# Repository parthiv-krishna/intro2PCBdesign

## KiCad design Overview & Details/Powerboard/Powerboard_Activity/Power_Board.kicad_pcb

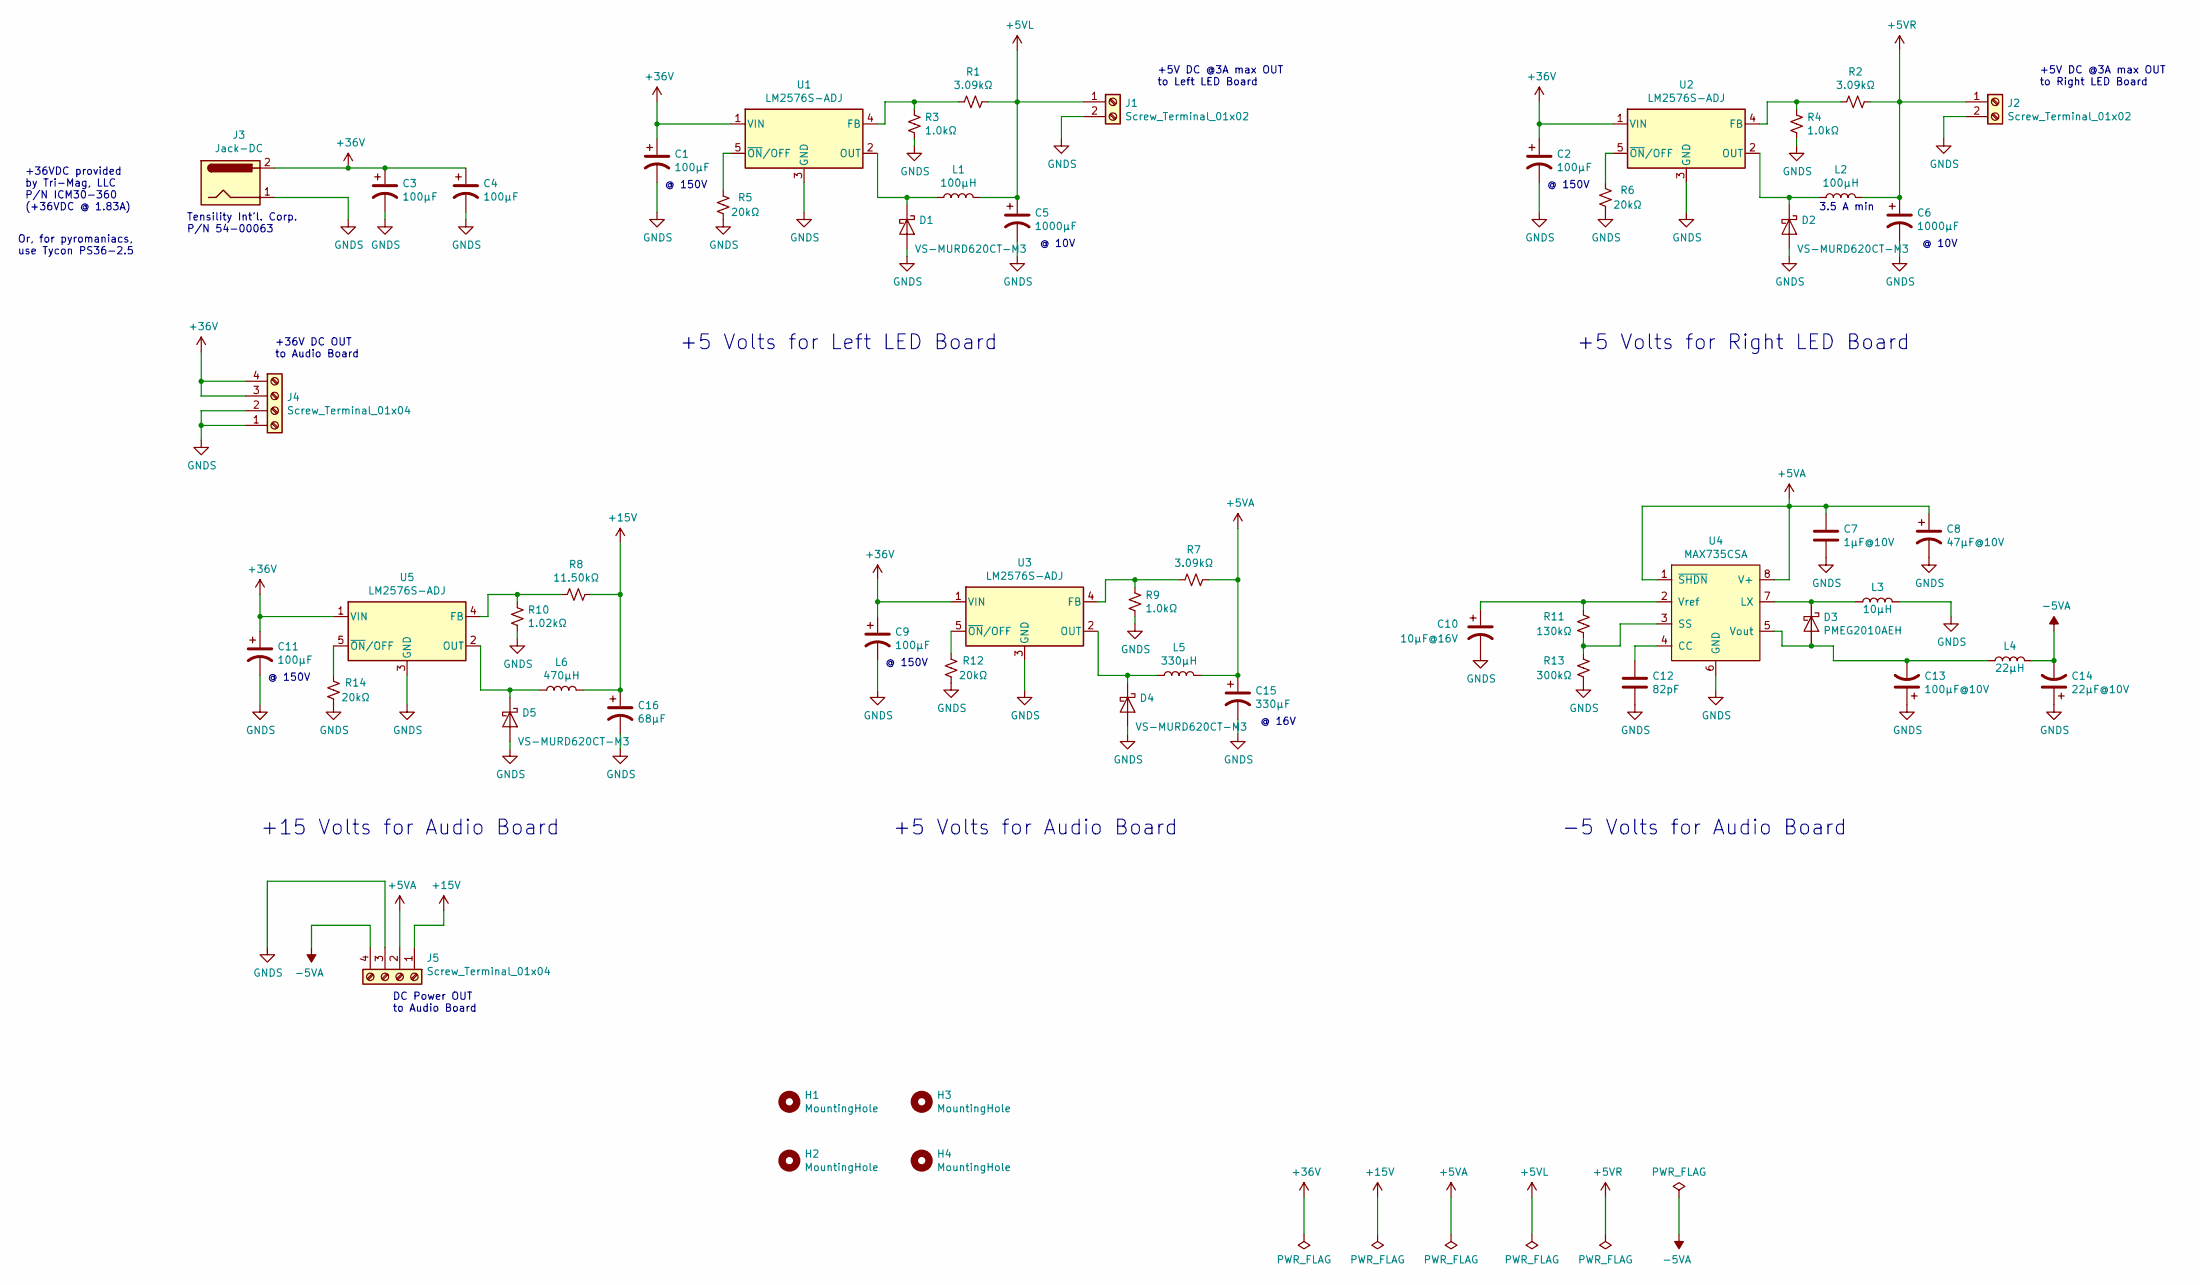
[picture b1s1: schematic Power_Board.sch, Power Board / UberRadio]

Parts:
C1, C2, C9, C11: 100µF; PCR1J101MCL1GS
C3, C4: 100μF; PCR1J101MCL1GS
C5, C6: 1000µF; CP_EIA-7361-438_AVX-U_Pad2.18x3.30mm_HandSolder
C7: 1μF@10V; C_0805_2012Metric_Pad1.15x1.40mm_HandSolder
C8: 47μF@10V; CP_Elec_6.3x5.7
C10: 10μF@16V; C_0805_2012Metric_Pad1.15x1.40mm_HandSolder
C12: 82pF; C_0805_2012Metric_Pad1.15x1.40mm_HandSolder
C13: 100μF@10V; C_1210_3225Metric_Pad1.42x2.65mm_HandSolder
C14: 22μF@10V; C_0805_2012Metric_Pad1.15x1.40mm_HandSolder
C15: 330µF; CP_Elec_8x10
C16: 68µF; CP_Elec_10x10
D1, D2, D4, D5: VS-MURD620CT-M3; TO-252AA_TabPin4
D3: PMEG2010AEH; D_SOD-123F
H1, H2, H3, H4: MountingHole; MountingHole_5.3mm_M5
J1, J2: Screw_Terminal_01x02; AVX-Wire-To-Board-1x2
J3: Jack-DC; BarrelJack_Power_2.1x5.5mm_11mmThruHole_PanelMount
J4, J5: Screw_Terminal_01x04; AVX-Wire-To-Board-1x4
L1, L2: 100µH; Eaton_CTX100-2-52-R
L3: 10μH; L_Taiyo-Yuden_NR-10050_9.8x10.0mm_HandSoldering
L4: 22μH; L_Taiyo-Yuden_NR-60xx_HandSoldering
L5: 330µH; L_Toroid_Horizontal_D21.8mm_P19.60mm_Bourns_2100
L6: 470µH; L_Toroid_Horizontal_D21.8mm_P19.60mm_Bourns_2100
R1, R2, R7: 3.09kΩ; R_0805_2012Metric_Pad1.15x1.40mm_HandSolder
R3, R4, R9: 1.0kΩ; R_0805_2012Metric_Pad1.15x1.40mm_HandSolder
R5, R6, R12, R14: 20kΩ; R_0805_2012Metric_Pad1.15x1.40mm_HandSolder
R8: 11.50kΩ; R_0805_2012Metric_Pad1.15x1.40mm_HandSolder
R10: 1.02kΩ; R_0805_2012Metric_Pad1.15x1.40mm_HandSolder
R11: 130kΩ; R_0805_2012Metric_Pad1.15x1.40mm_HandSolder
R13: 300kΩ; R_0805_2012Metric_Pad1.15x1.40mm_HandSolder
U1, U2, U3, U5: LM2576S-ADJ; TO-263-5_TabPin3
U4: MAX735CSA; SOP-8_3.9x4.9mm_P1.27mm

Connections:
+5VA: C7.1, C8.1, C15.1, J5.2, L5.2, R7.1, U4.1 (~SHDN), U4.8 (V+)
+5VL: C5.1, J1.1, L1.2, R1.1
+5VR: C6.1, J2.1, L2.2, R2.1
+15V: C16.1, J5.1, L6.2, R8.1
+36V: C1.1, C2.1, C3.1, C4.1, C9.1, C11.1, J3.2, J4.3 (Pin_2), J4.4 (Pin_1), U1.1 (VIN), U2.1 (VIN), U3.1 (VIN), U5.1 (VIN)
-5VA: C14.2, J5.4, L4.2
GNDS: C1.2, C2.2, C3.2, C4.2, C5.2, C6.2, C7.2, C8.2, C9.2, C10.2, C11.2, C12.2, C13.1, C14.1, C15.2, C16.2, D1.2 (A), D2.2 (A), D4.2 (A), D5.2 (A), J1.2, J2.2, J3.1, J4.1 (Pin_4), J4.2 (ePin_3), J5.3, L3.2, R3.1, R4.1, R5.1, R6.1, R9.1, R10.1, R12.1, R13.2, R14.1, U1.3 (GND), U2.3 (GND), U3.3 (GND), U4.6 (GND), U5.3 (GND)
unnamed: C10.1, R11.1, U4.2 (Vref)
unnamed: C12.1, U4.4 (CC)
unnamed: C13.2, D3.2 (A), L4.1, U4.5 (Vout)
unnamed: D1.1 (K), L1.1, U1.2 (OUT)
unnamed: D2.1 (K), L2.1, U2.2 (OUT)
unnamed: D3.1 (K), L3.1, U4.7 (LX)
unnamed: D4.1 (K), L5.1, U3.2 (OUT)
unnamed: D5.1 (K), L6.1, U5.2 (OUT)
unnamed: R1.2, R3.2, U1.4 (FB)
unnamed: R2.2, R4.2, U2.4 (FB)
unnamed: R5.2, U1.5 (~ON~/OFF)
unnamed: R6.2, U2.5 (~ON~/OFF)
unnamed: R7.2, R9.2, U3.4 (FB)
unnamed: R8.2, R10.2, U5.4 (FB)
unnamed: R11.2, R13.1, U4.3 (SS)
unnamed: R12.2, U3.5 (~ON~/OFF)
unnamed: R14.2, U5.5 (~ON~/OFF)

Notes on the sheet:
Tensility Int’l. Corp. P/N 54-00063
+36VDC provided by Tri-Mag, LLC P/N ICM30-360 (+36VDC @ 1.83A)
Or, for pyromaniacs, use Tycon PS36-2.5
+5 Volts for Left LED Board
+5 Volts for Right LED Board
+15 Volts for Audio Board
+5 Volts for Audio Board
-5 Volts for Audio Board
@ 150V
3.5 A min
@ 10V
@ 16V
+36V DC OUT to Audio Board
DC Power OUT to Audio Board
+5V DC @3A max OUT to Left LED Board
+5V DC @3A max OUT to Right LED Board

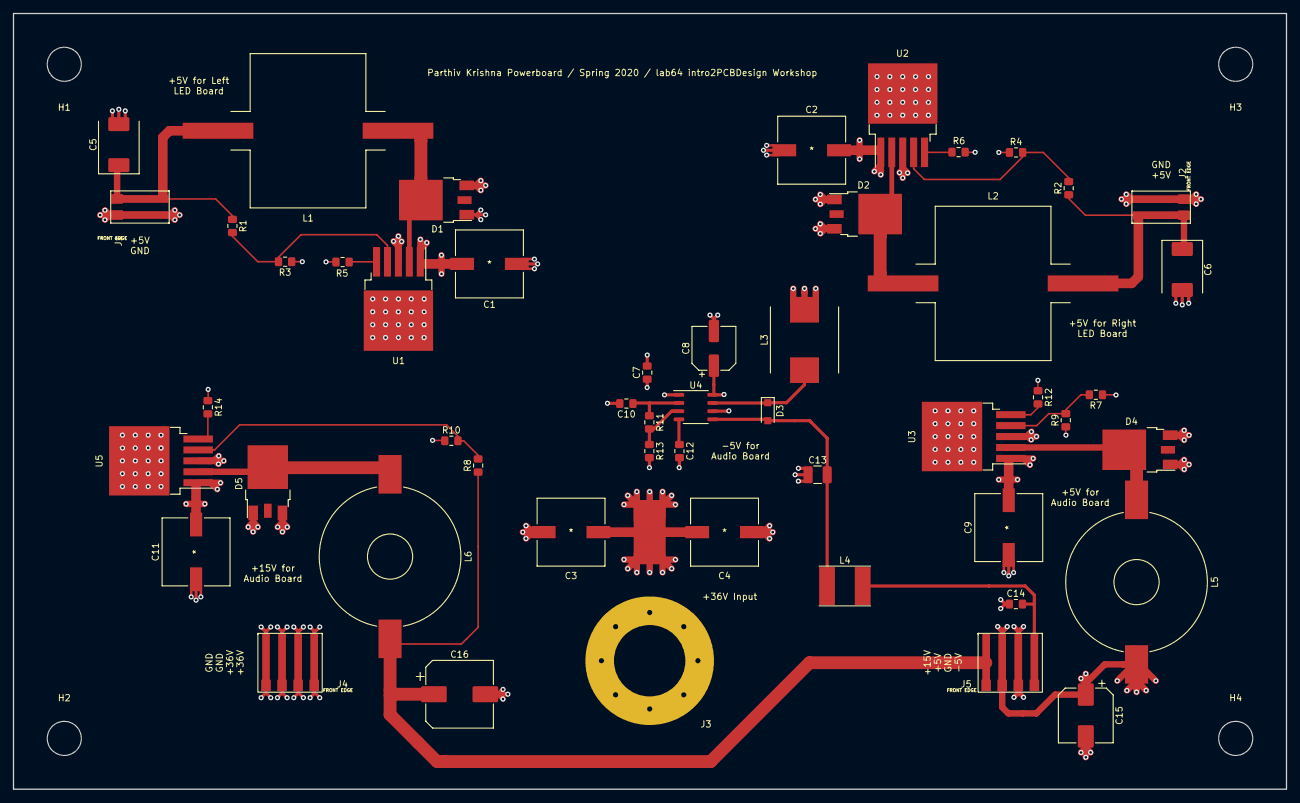
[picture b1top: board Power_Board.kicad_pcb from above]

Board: 4 copper layers, 198.0 x 120.7 mm, 55 parts (0 on the bottom side), 24 nets.

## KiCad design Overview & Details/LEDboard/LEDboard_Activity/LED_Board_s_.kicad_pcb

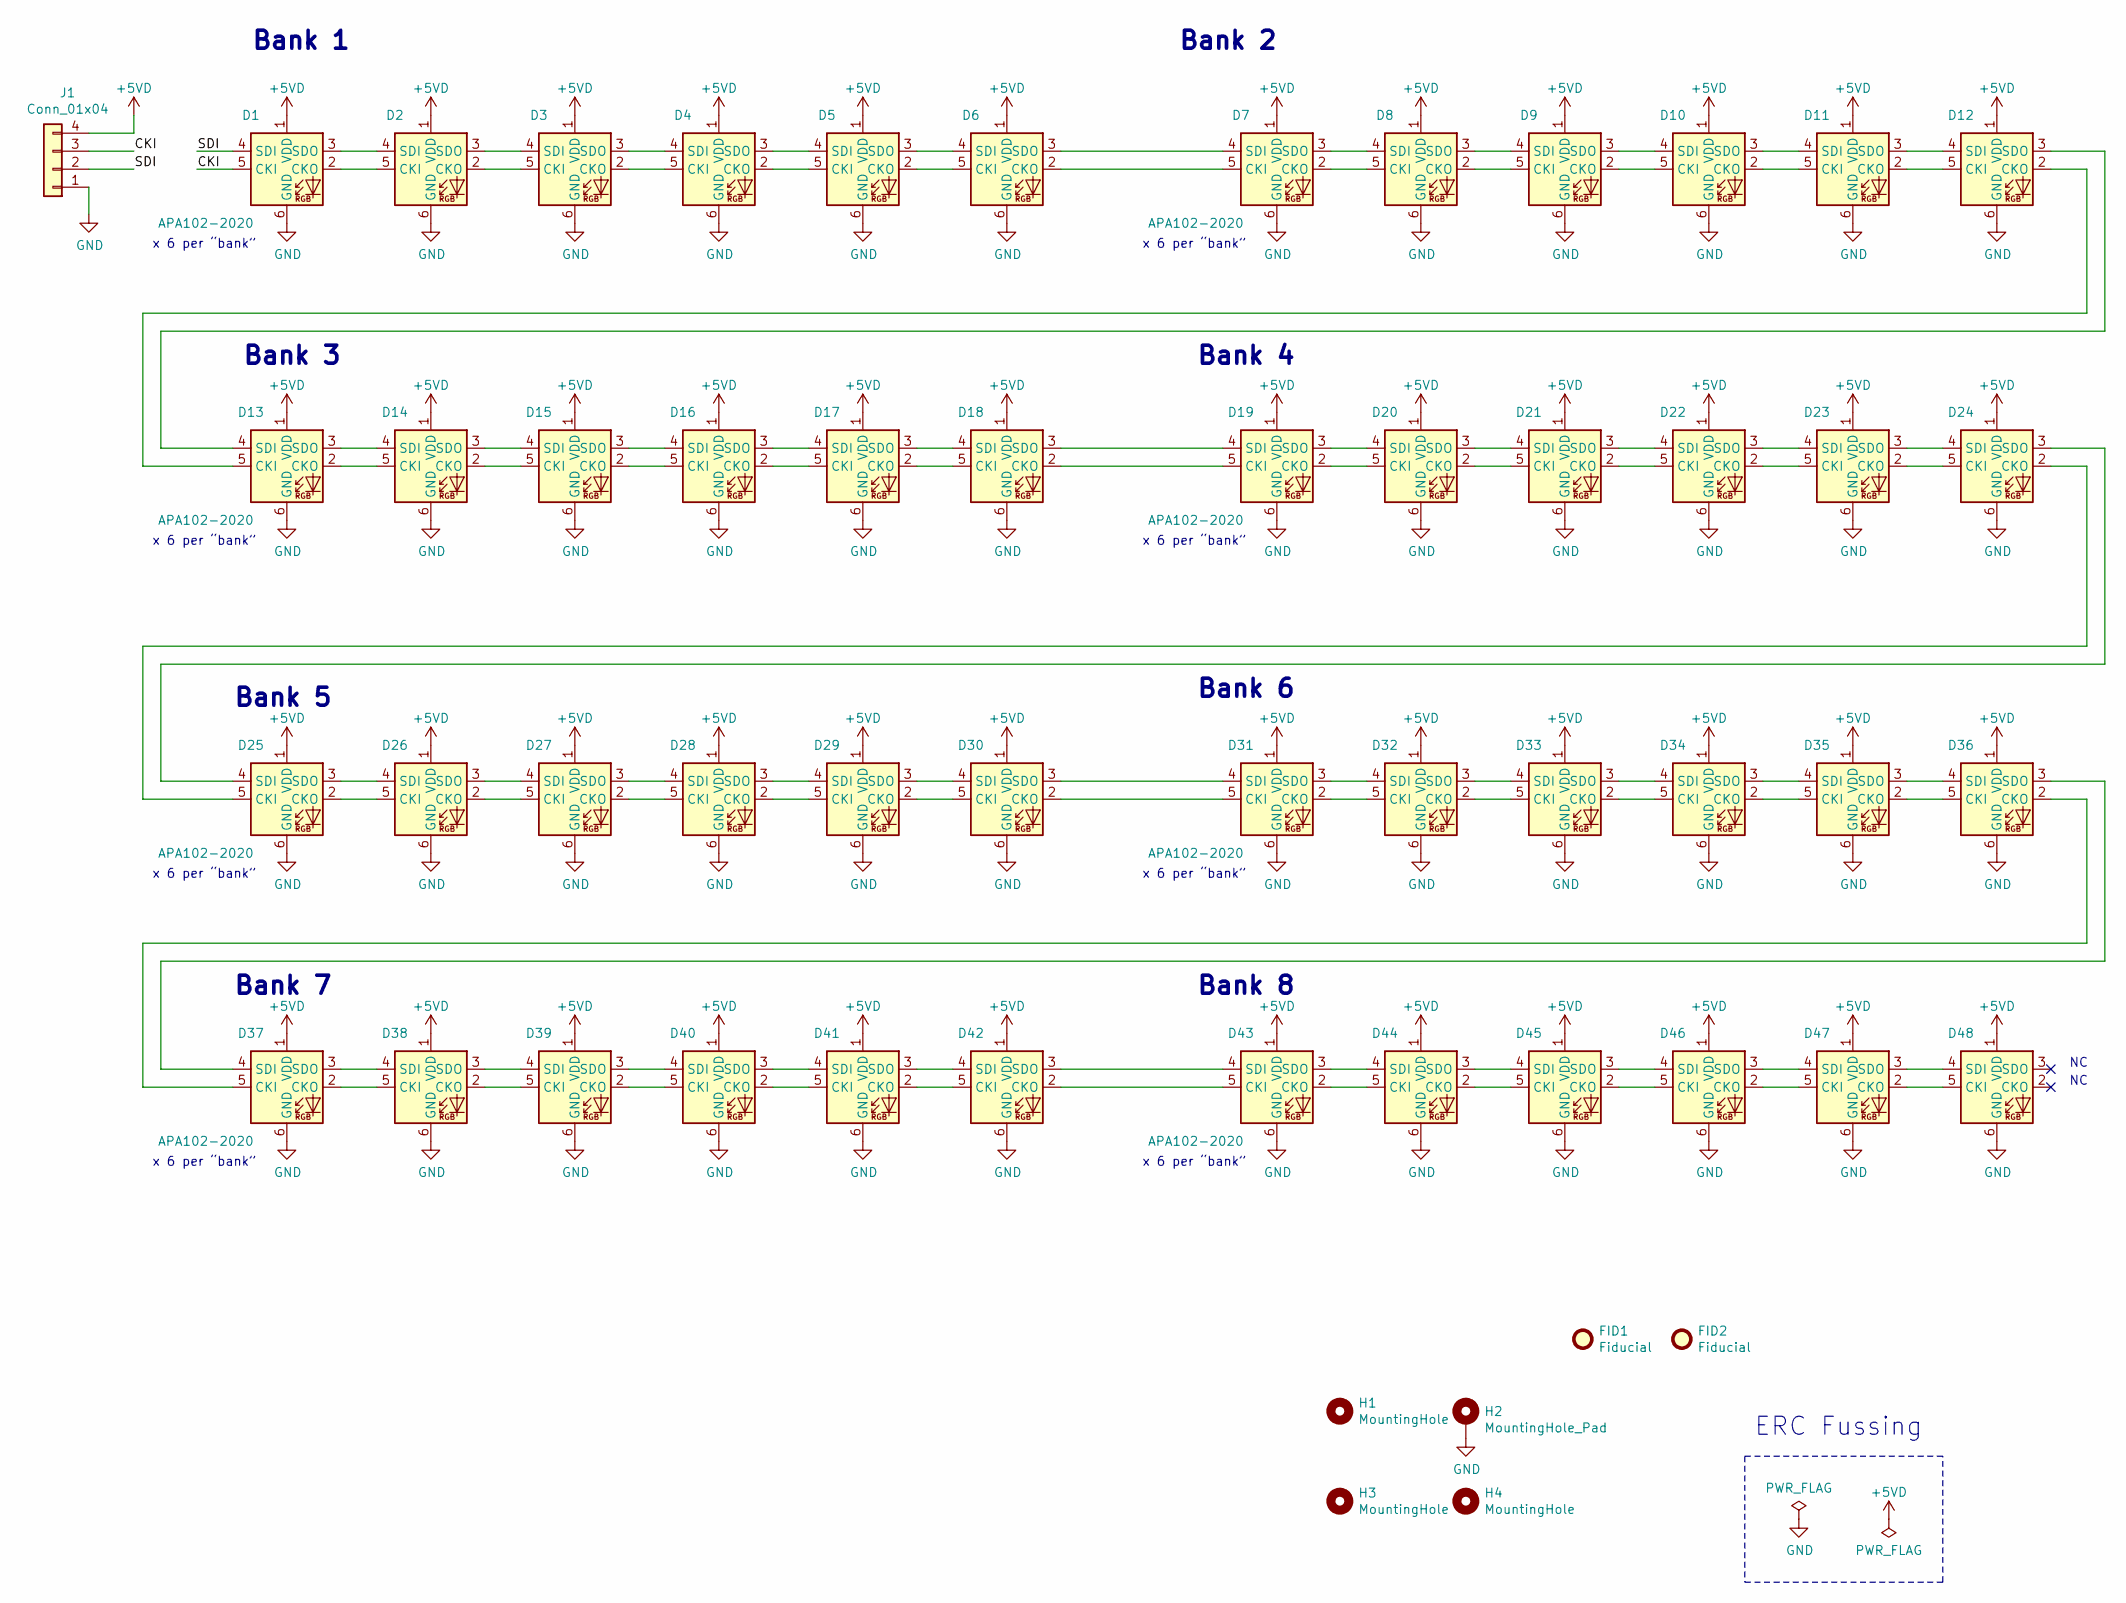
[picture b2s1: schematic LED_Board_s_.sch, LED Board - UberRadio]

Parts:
D1, D2, D3, D4, D5, D6, D7, D8, D9, D10, D11, D12, D13, D14, D15, D16, D17, D18, D19, D20, D21, D22, D23, D24, D25, D26, D27, D28, D29, D30, D31, D32, D33, D34, D35, D36, D37, D38, D39, D40, D41, D42, D43, D44, D45, D46, D47, D48: APA102-2020; LED-APA102-2020
FID1, FID2: Fiducial; Fiducial_0.5mm_Mask1mm
H1, H3, H4: MountingHole; MountingHole_3.5mm_Pad
H2: MountingHole_Pad; MountingHole_3.5mm_Pad_Via
J1: Conn_01x04; PinHeader_1x04_P2.54mm_Vertical

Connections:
+5VD: D1.1 (VDD), D2.1 (VDD), D3.1 (VDD), D4.1 (VDD), D5.1 (VDD), D6.1 (VDD), D7.1 (VDD), D8.1 (VDD), D9.1 (VDD), D10.1 (VDD), D11.1 (VDD), D12.1 (VDD), D13.1 (VDD), D14.1 (VDD), D15.1 (VDD), D16.1 (VDD), D17.1 (VDD), D18.1 (VDD), D19.1 (VDD), D20.1 (VDD), D21.1 (VDD), D22.1 (VDD), D23.1 (VDD), D24.1 (VDD), D25.1 (VDD), D26.1 (VDD), D27.1 (VDD), D28.1 (VDD), D29.1 (VDD), D30.1 (VDD), D31.1 (VDD), D32.1 (VDD), D33.1 (VDD), D34.1 (VDD), D35.1 (VDD), D36.1 (VDD), D37.1 (VDD), D38.1 (VDD), D39.1 (VDD), D40.1 (VDD), D41.1 (VDD), D42.1 (VDD), D43.1 (VDD), D44.1 (VDD), D45.1 (VDD), D46.1 (VDD), D47.1 (VDD), D48.1 (VDD), J1.4
/CKI: D1.5 (CKI), J1.3
/SDI: D1.4 (SDI), J1.2
GND: D1.6 (GND), D2.6 (GND), D3.6 (GND), D4.6 (GND), D5.6 (GND), D6.6 (GND), D7.6 (GND), D8.6 (GND), D9.6 (GND), D10.6 (GND), D11.6 (GND), D12.6 (GND), D13.6 (GND), D14.6 (GND), D15.6 (GND), D16.6 (GND), D17.6 (GND), D18.6 (GND), D19.6 (GND), D20.6 (GND), D21.6 (GND), D22.6 (GND), D23.6 (GND), D24.6 (GND), D25.6 (GND), D26.6 (GND), D27.6 (GND), D28.6 (GND), D29.6 (GND), D30.6 (GND), D31.6 (GND), D32.6 (GND), D33.6 (GND), D34.6 (GND), D35.6 (GND), D36.6 (GND), D37.6 (GND), D38.6 (GND), D39.6 (GND), D40.6 (GND), D41.6 (GND), D42.6 (GND), D43.6 (GND), D44.6 (GND), D45.6 (GND), D46.6 (GND), D47.6 (GND), D48.6 (GND), H2.1, J1.1
unnamed: D1.2 (CKO), D2.5 (CKI)
unnamed: D1.3 (SDO), D2.4 (SDI)
unnamed: D2.2 (CKO), D3.5 (CKI)
unnamed: D2.3 (SDO), D3.4 (SDI)
unnamed: D3.2 (CKO), D4.5 (CKI)
unnamed: D3.3 (SDO), D4.4 (SDI)
unnamed: D4.2 (CKO), D5.5 (CKI)
unnamed: D4.3 (SDO), D5.4 (SDI)
unnamed: D5.2 (CKO), D6.5 (CKI)
unnamed: D5.3 (SDO), D6.4 (SDI)
unnamed: D6.2 (CKO), D7.5 (CKI)
unnamed: D6.3 (SDO), D7.4 (SDI)
unnamed: D7.2 (CKO), D8.5 (CKI)
unnamed: D7.3 (SDO), D8.4 (SDI)
unnamed: D8.2 (CKO), D9.5 (CKI)
unnamed: D8.3 (SDO), D9.4 (SDI)
unnamed: D10.2 (CKO), D11.5 (CKI)
unnamed: D10.3 (SDO), D11.4 (SDI)
unnamed: D9.3 (SDO), D10.4 (SDI)
unnamed: D9.2 (CKO), D10.5 (CKI)
unnamed: D11.2 (CKO), D12.5 (CKI)
unnamed: D11.3 (SDO), D12.4 (SDI)
unnamed: D12.2 (CKO), D13.5 (CKI)
unnamed: D12.3 (SDO), D13.4 (SDI)
unnamed: D13.2 (CKO), D14.5 (CKI)
unnamed: D13.3 (SDO), D14.4 (SDI)
unnamed: D14.2 (CKO), D15.5 (CKI)
unnamed: D14.3 (SDO), D15.4 (SDI)
unnamed: D15.2 (CKO), D16.5 (CKI)
unnamed: D15.3 (SDO), D16.4 (SDI)
unnamed: D16.2 (CKO), D17.5 (CKI)
unnamed: D16.3 (SDO), D17.4 (SDI)
unnamed: D17.2 (CKO), D18.5 (CKI)
unnamed: D17.3 (SDO), D18.4 (SDI)
unnamed: D18.2 (CKO), D19.5 (CKI)
unnamed: D18.3 (SDO), D19.4 (SDI)
unnamed: D19.2 (CKO), D20.5 (CKI)
unnamed: D19.3 (SDO), D20.4 (SDI)
unnamed: D20.2 (CKO), D21.5 (CKI)
unnamed: D20.3 (SDO), D21.4 (SDI)
unnamed: D21.2 (CKO), D22.5 (CKI)
unnamed: D21.3 (SDO), D22.4 (SDI)
unnamed: D22.2 (CKO), D23.5 (CKI)
unnamed: D22.3 (SDO), D23.4 (SDI)
unnamed: D23.2 (CKO), D24.5 (CKI)
unnamed: D23.3 (SDO), D24.4 (SDI)
unnamed: D24.2 (CKO), D25.5 (CKI)
unnamed: D24.3 (SDO), D25.4 (SDI)
unnamed: D25.2 (CKO), D26.5 (CKI)
unnamed: D25.3 (SDO), D26.4 (SDI)
unnamed: D26.2 (CKO), D27.5 (CKI)
unnamed: D26.3 (SDO), D27.4 (SDI)
unnamed: D27.2 (CKO), D28.5 (CKI)
unnamed: D27.3 (SDO), D28.4 (SDI)
unnamed: D28.2 (CKO), D29.5 (CKI)
unnamed: D28.3 (SDO), D29.4 (SDI)
unnamed: D29.2 (CKO), D30.5 (CKI)
unnamed: D29.3 (SDO), D30.4 (SDI)
unnamed: D30.2 (CKO), D31.5 (CKI)
unnamed: D30.3 (SDO), D31.4 (SDI)
unnamed: D31.2 (CKO), D32.5 (CKI)
unnamed: D31.3 (SDO), D32.4 (SDI)
unnamed: D32.2 (CKO), D33.5 (CKI)
unnamed: D32.3 (SDO), D33.4 (SDI)
unnamed: D33.2 (CKO), D34.5 (CKI)
unnamed: D33.3 (SDO), D34.4 (SDI)
unnamed: D34.2 (CKO), D35.5 (CKI)
unnamed: D34.3 (SDO), D35.4 (SDI)
unnamed: D35.2 (CKO), D36.5 (CKI)
unnamed: D35.3 (SDO), D36.4 (SDI)
unnamed: D36.2 (CKO), D37.5 (CKI)
unnamed: D36.3 (SDO), D37.4 (SDI)
unnamed: D37.2 (CKO), D38.5 (CKI)
unnamed: D37.3 (SDO), D38.4 (SDI)
unnamed: D38.2 (CKO), D39.5 (CKI)
unnamed: D38.3 (SDO), D39.4 (SDI)
unnamed: D39.2 (CKO), D40.5 (CKI)
unnamed: D39.3 (SDO), D40.4 (SDI)
unnamed: D40.2 (CKO), D41.5 (CKI)
unnamed: D40.3 (SDO), D41.4 (SDI)
unnamed: D41.2 (CKO), D42.5 (CKI)
unnamed: D41.3 (SDO), D42.4 (SDI)
unnamed: D42.2 (CKO), D43.5 (CKI)
unnamed: D42.3 (SDO), D43.4 (SDI)
unnamed: D43.2 (CKO), D44.5 (CKI)
unnamed: D43.3 (SDO), D44.4 (SDI)
unnamed: D44.2 (CKO), D45.5 (CKI)
unnamed: D44.3 (SDO), D45.4 (SDI)
unnamed: D45.2 (CKO), D46.5 (CKI)
unnamed: D45.3 (SDO), D46.4 (SDI)
unnamed: D46.2 (CKO), D47.5 (CKI)
unnamed: D46.3 (SDO), D47.4 (SDI)
unnamed: D47.2 (CKO), D48.5 (CKI)
unnamed: D47.3 (SDO), D48.4 (SDI)

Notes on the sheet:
x 6 per “bank”
Bank 1
Bank 2
Bank 3
Bank 5
Bank 7
Bank 4
Bank 6
Bank 8
ERC Fussing

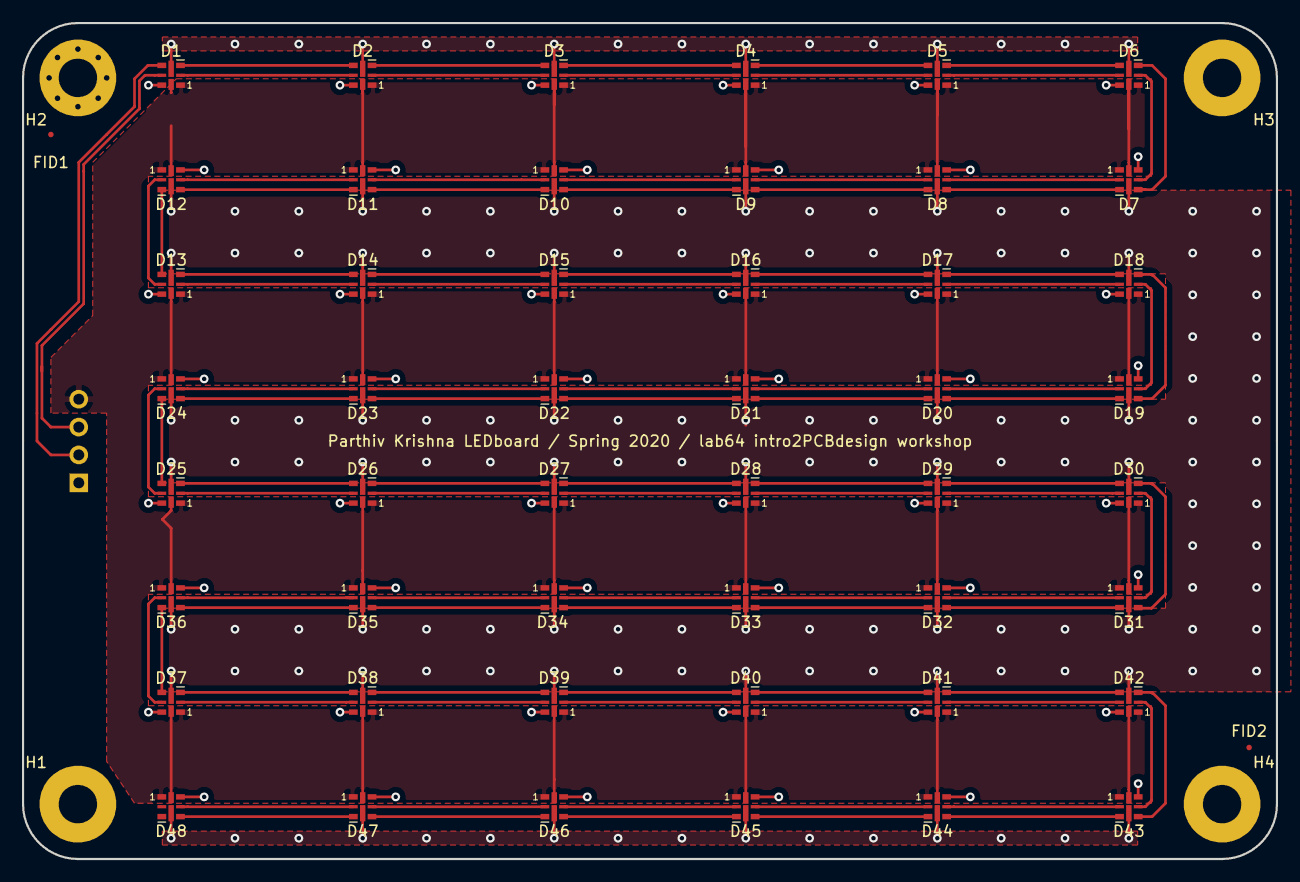
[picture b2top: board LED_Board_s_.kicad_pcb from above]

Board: 2 copper layers, 114.3 x 76.2 mm, 55 parts (1 on the bottom side), 98 nets.

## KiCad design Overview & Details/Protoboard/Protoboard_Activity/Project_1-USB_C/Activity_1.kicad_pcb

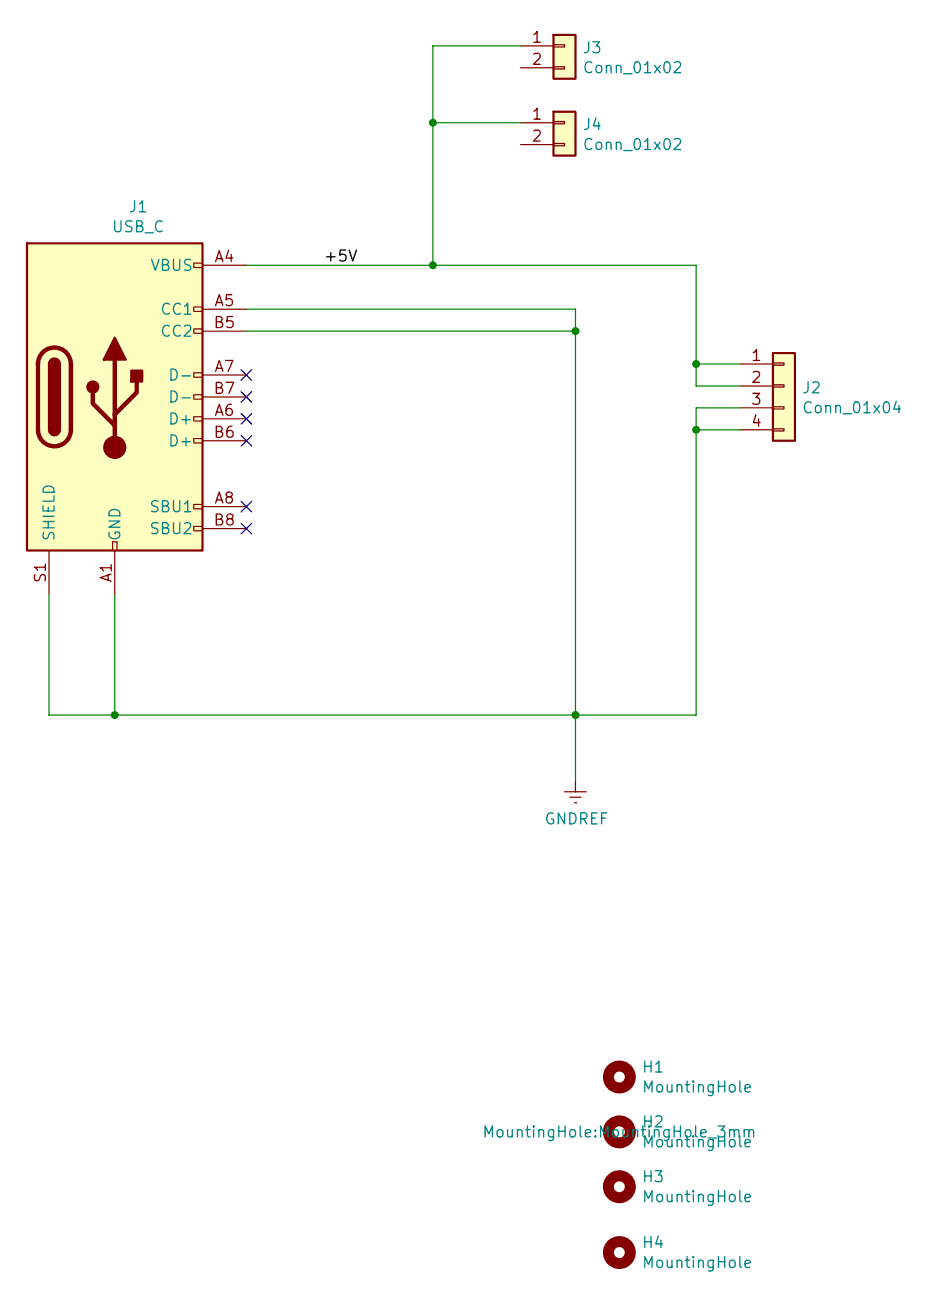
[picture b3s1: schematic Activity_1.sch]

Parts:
H1, H2, H3, H4: MountingHole; MountingHole_3mm
J1: USB_C; USB_C_Receptacle
J2: Conn_01x04; PinHeader_1x04_P2.54mm_Vertical
J3, J4: Conn_01x02; PinSocket_1x02_P2.54mm_Vertical

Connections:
/+5V: J1.A4 (VBUS), J1.A9 (VBUS), J2.1, J2.2, J3.1, J4.1
GNDREF: J1.A1 (GND), J1.A5 (CC1), J1.A12 (GND), J1.B5 (CC2), J1.S1 (SHIELD), J2.3, J2.4

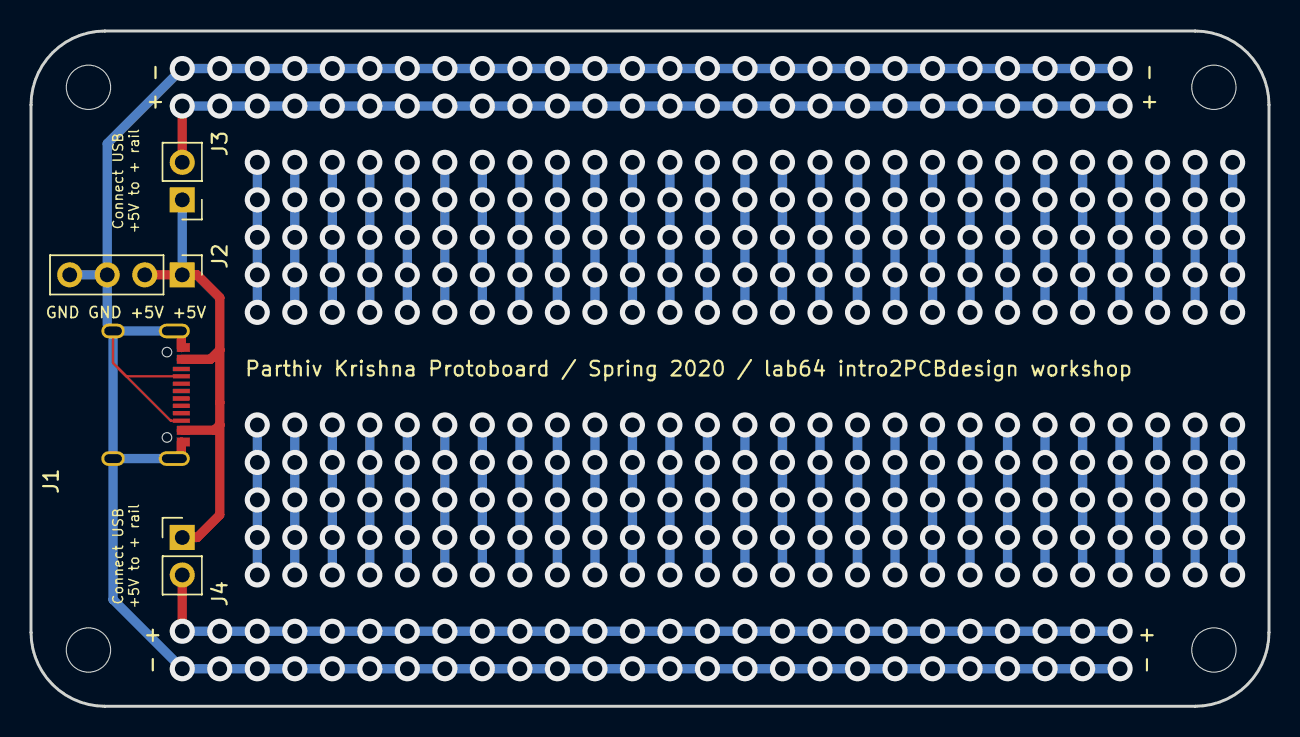
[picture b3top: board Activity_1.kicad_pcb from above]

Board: 2 copper layers, 83.8 x 45.7 mm, 8 parts (0 on the bottom side), 2 nets.

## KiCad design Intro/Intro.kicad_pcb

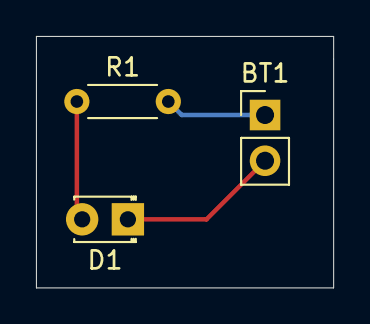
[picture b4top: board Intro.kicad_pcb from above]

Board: 2 copper layers, 16.5 x 14.0 mm, 3 parts (0 on the bottom side), 3 nets.

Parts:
BT1: 9V; PinHeader_1x02_P2.54mm_Vertical
D1: LED; LED_D1.8mm_W3.3mm_H2.4mm
R1: 470; R_Axial_DIN0204_L3.6mm_D1.6mm_P5.08mm_Horizontal

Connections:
unnamed: BT1.1, R1.2
unnamed: BT1.2, D1.1
unnamed: D1.2, R1.1

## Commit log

2020-04-15 Created intro project
    simple LED PCB
2020-04-18 Create custom board outline
2020-04-18 Activity 1 schematic
2020-04-18 Shrink outline a bit
2020-04-18 Create PCB
2020-04-20 Finish pcb and generate gerbers
2020-04-20 Zip gerbers
2020-04-24 Create LEDboard schematic
2020-04-24 Place components
2020-04-24 add fiducials
2020-04-27 finish LEDboard PCB
2020-04-27 add labels to connector
2020-04-27 LEDboard gerbers
2020-05-14 powerboard schematic
2020-05-14 remove problematic footprint association
2020-05-21 Pre-board review
2020-05-22 Finish powerboard design

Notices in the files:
parts and their libraries:
Copyright 2016 Accelerated Designs. All rights reserved.
